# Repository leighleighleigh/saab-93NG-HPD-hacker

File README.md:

# saab-93NG-HPD-hacker
A reverse-engineering and interfacing board for the Saab Information Display / High Position Display, on 2003-2006 9-3 (Second Generation) Models.

## Project Status (DEC **2021**)
The **third** prototype of the PCB has been assembled and tested, as of August **2020**.
During this testing period, mild success was had, and some text/images were displayed. The full protocol is yet to be determined.

## Protocol Reverse Engineering
Please see [UART PROTOCOL](/UART_PROTOCOL.md) 

## Hardware Diagram
### Full In-car System

### HPD Interface v3 Internals (WIP)
The HPD hacker is unusual in that it utilises a dedicated UART interface accesible over SPI.
This eliminates the need for dedicated UART interfaces on the host microcontroller, which was a concern when the original design targeted the ESP8266.
The ESP32 series has enough hardware UARTs to do this on it's own, which will be utilised in the next hardware revision.

## Project structure
```bash
├── data_dumps # Raw UART data, CSV files exported from 'KingstVIS' software
├── hardware # KICAD v5+ projects
├── media # Images and diagrams
├── software # PlatformIO projects for the microcontrollers used here
└── PROTOCOL.md # This is where the results of our efforts is stored
```

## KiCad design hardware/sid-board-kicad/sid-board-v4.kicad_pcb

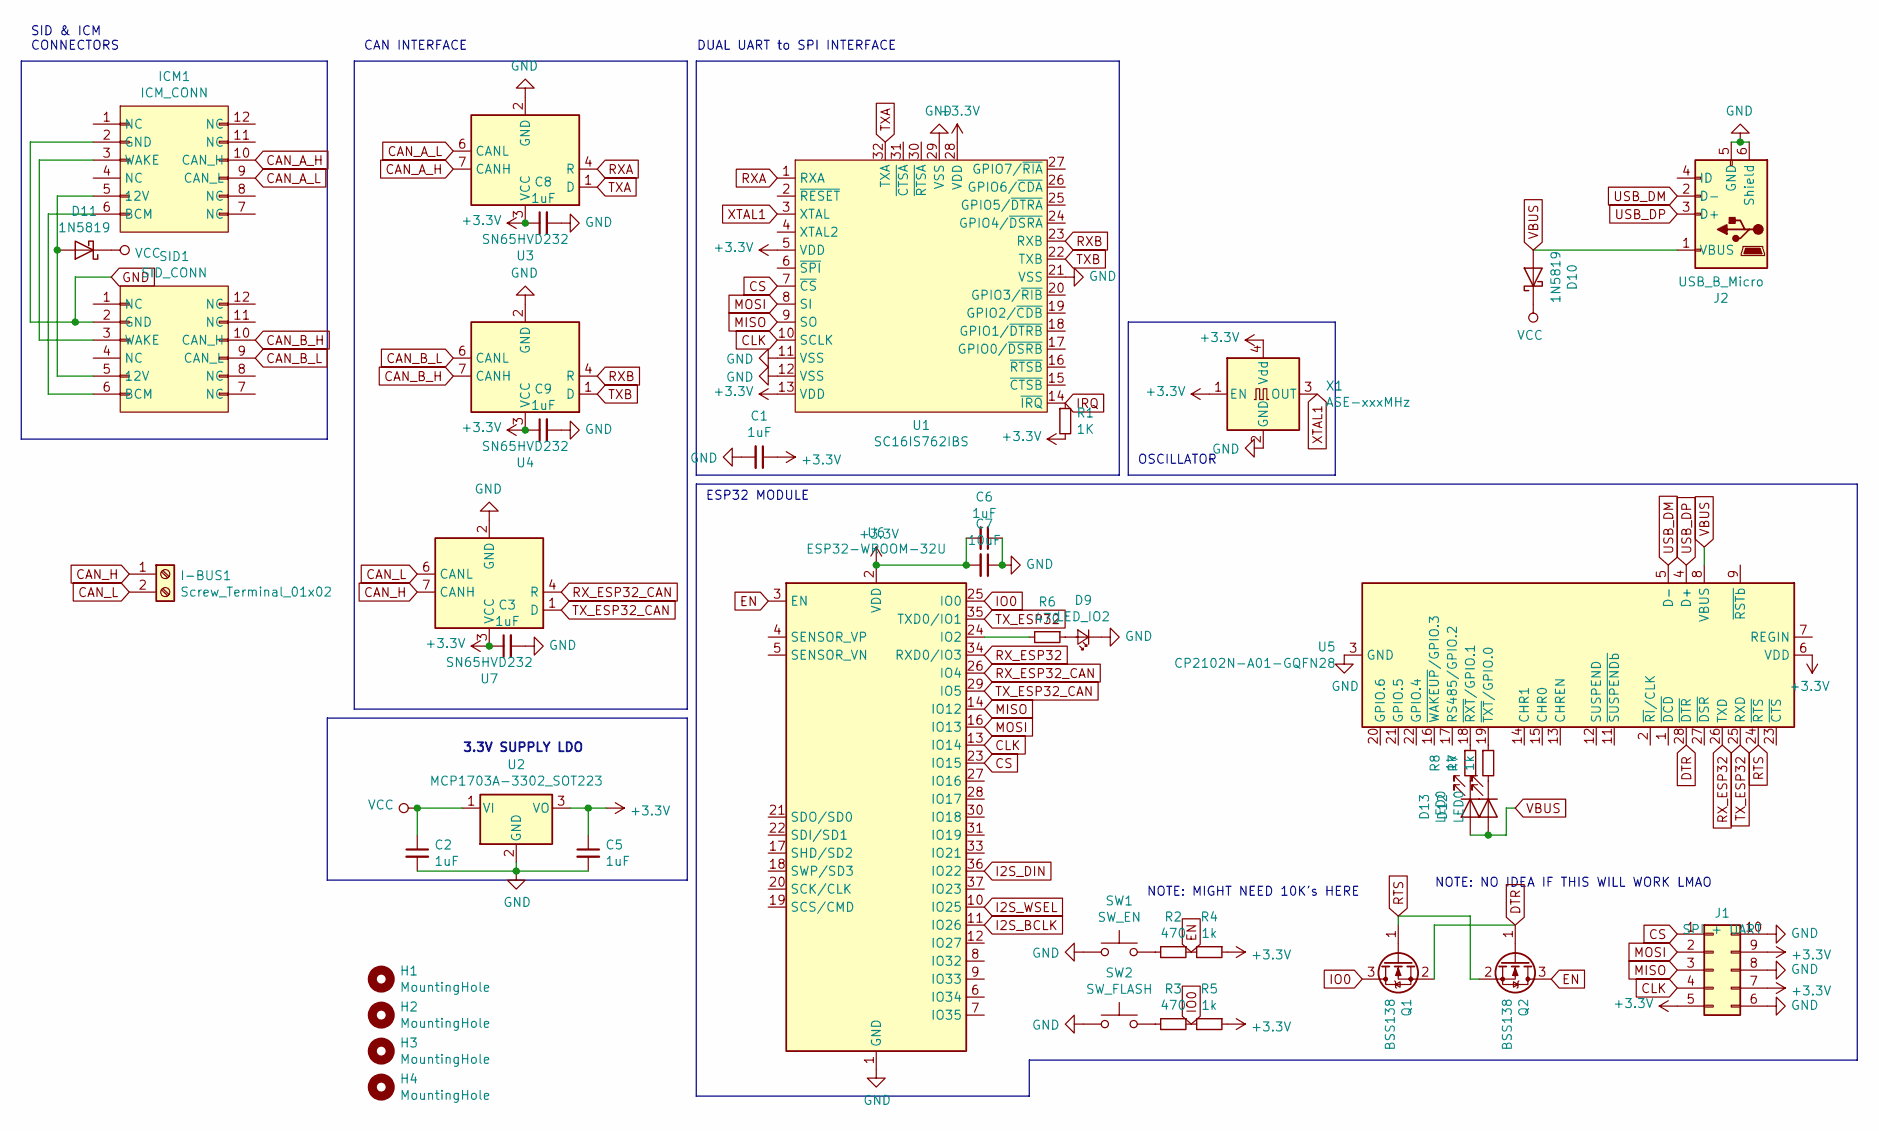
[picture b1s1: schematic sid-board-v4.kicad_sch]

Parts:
C1, C2, C3, C5, C6, C8, C9: 1uF; C_0805_2012Metric_Pad1.15x1.40mm_HandSolder
C7: 10uF; CP_EIA-6032-20_AVX-F_Pad2.25x2.35mm_HandSolder
D9: LED_IO2; LED_0805_2012Metric_Pad1.15x1.40mm_HandSolder
D10, D11: 1N5819; D_SOD-123
D12, D13: LED0; LED_0805_2012Metric_Pad1.15x1.40mm_HandSolder
H1, H2, H3, H4: MountingHole; MountingHole_4.3mm_M4_Pad_Via
I-BUS1: Screw_Terminal_01x02; TerminalBlock_Phoenix_MKDS-1,5-2-5.08_1x02_P5.08mm_Horizont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
ICM1: ICM_CONN; SAAB_SID_CONNECTOR_HEADER
J1: SPI + UART; PinHeader_2x05_P2.00mm_Vertical
J2: USB_B_Micro; USB_Micro-B_Molex-105017-0001
Q1, Q2: BSS138; SOT-23
R1: 1K; R_0805_2012Metric_Pad1.15x1.40mm_HandSolder
R2, R3, R6: 470; R_0805_2012Metric_Pad1.15x1.40mm_HandSolder
R4, R5, R7, R8: 1k; R_0805_2012Metric_Pad1.15x1.40mm_HandSolder
SID1: SID_CONN; SAAB_SID_CONNECTOR_HEADER
SW1: SW_EN; SW_Push_SPST_NO_Alps_SKRK
SW2: SW_FLASH; SW_Push_SPST_NO_Alps_SKRK
U1: SC16IS762IBS; VQFN-32-1EP_5x5mm_P0.5mm_EP3.1x3.1mm
U2: MCP1703A-3302_SOT223; SOT-223-3_TabPin2
U3, U4, U7: SN65HVD232; SOIC-8_3.9x4.9mm_P1.27mm
U5: CP2102N-A01-GQFN28; QFN-28-1EP_5x5mm_P0.5mm_EP3.35x3.35mm
U6: ESP32-WROOM-32U
X1: ASE-xxxMHz; Oscillator_SMD_EuroQuartz_XO53-4Pin_5.0x3.2mm_HandSoldering

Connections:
+3V3: C1.1, C3.1, C5.1, C6.2, C7.2, C8.1, C9.1, J1.5, J1.7, J1.9, R1.2, R4.1, R5.1, U1.5 (VDD), U1.13 (VDD), U1.28 (VDD), U2.3 (VO), U3.3 (VCC), U4.3 (VCC), U5.6 (VDD), U6.2 (VDD), U7.3 (VCC), X1.1 (EN), X1.4 (Vdd)
CAN_A_H: ICM1.10 (CAN_H), U3.7 (CANH)
CAN_A_L: ICM1.9 (CAN_L), U3.6 (CANL)
CAN_B_H: SID1.10 (CAN_H), U4.7 (CANH)
CAN_B_L: SID1.9 (CAN_L), U4.6 (CANL)
CAN_H: I-BUS1.1, U7.7 (CANH)
CAN_L: I-BUS1.2, U7.6 (CANL)
CLK: J1.4, U1.10 (SCLK), U6.13 (IO14)
CS: J1.1, U1.7 (~CS), U6.23 (IO15)
DTR: Q1.2 (S), Q2.1 (G), U5.28 (~DTR)
EN: Q2.3 (D), R2.1, R4.2, U6.3 (EN)
GND: C1.2, C2.2, C3.2, C5.2, C6.1, C7.1, C8.2, C9.2, D9.1 (K), ICM1.2 (GND), J1.6, J1.8, J1.10, J2.5 (GND), J2.6 (Shield), SID1.2 (GND), SW1.1, SW2.1, U1.11 (VSS), U1.12 (VSS), U1.21 (VSS), U1.29 (VSS), U2.2 (GND), U3.2 (GND), U4.2 (GND), U5.3 (GND), U5.29 (GND), U6.1 (GND), U6.15 (GND), U6.38 (GND), U6.39 (GND), U7.2 (GND), X1.2 (GND); also elsewhere on the board
I2S_BCLK: U6.11 (IO26)
I2S_DIN: U6.36 (IO22)
I2S_WSEL: U6.10 (IO25)
IO0: Q1.3 (D), R3.1, R5.2, U6.25 (IO0)
IRQ: R1.1, U1.14 (~IRQ)
MISO: J1.3, U1.9 (SO), U6.14 (IO12)
MOSI: J1.2, U1.8 (SI), U6.16 (IO13)
unnamed: D9.2 (A), R6.1
unnamed: D11.2 (A), ICM1.5 (12V), SID1.5 (12V)
unnamed: D12.1 (K), R7.2
unnamed: D13.1 (K), R8.2
unnamed: ICM1.3 (WAKE), SID1.3 (WAKE)
unnamed: ICM1.6 (BCM), SID1.6 (BCM)
unnamed: R2.2, SW1.2
unnamed: R3.2, SW2.2
unnamed: R6.2, U6.24 (IO2)
unnamed: R7.1, U5.19 (~TXT~/GPIO.0)
unnamed: R8.1, U5.18 (~RXT~/GPIO.1)
RTS: Q1.1 (G), Q2.2 (S), U5.24 (~RTS)
RXA: U1.1 (RXA), U3.4 (R)
RXB: U1.23 (RXB), U4.4 (R)
RX_ESP32: U5.26 (TXD), U6.34 (RXD0/IO3)
RX_ESP32_CAN: U6.26 (IO4), U7.4 (R)
TXA: U1.32 (TXA), U3.1 (D)
TXB: U1.22 (TXB), U4.1 (D)
TX_ESP32: U5.25 (RXD), U6.35 (TXD0/IO1)
TX_ESP32_CAN: U6.29 (IO5), U7.1 (D)
USB_DM: J2.2 (D-), U5.5 (D-); also elsewhere on the board
USB_DP: J2.3 (D+), U5.4 (D+); also elsewhere on the board
VBUS: D10.2 (A), D12.2 (A), D13.2 (A), J2.1 (VBUS), U5.8 (VBUS); also elsewhere on the board
VCC: C2.1, D10.1 (K), D11.1 (K), U2.1 (VI)
XTAL1: U1.3 (XTAL), X1.3 (OUT)

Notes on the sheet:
SID & ICM CONNECTORS
CAN INTERFACE
3.3V SUPPLY LDO
DUAL UART to SPI INTERFACE
ESP32 MODULE
OSCILLATOR
NOTE: MIGHT NEED 10K's HERE
NOTE: NO IDEA IF THIS WILL WORK LMAO

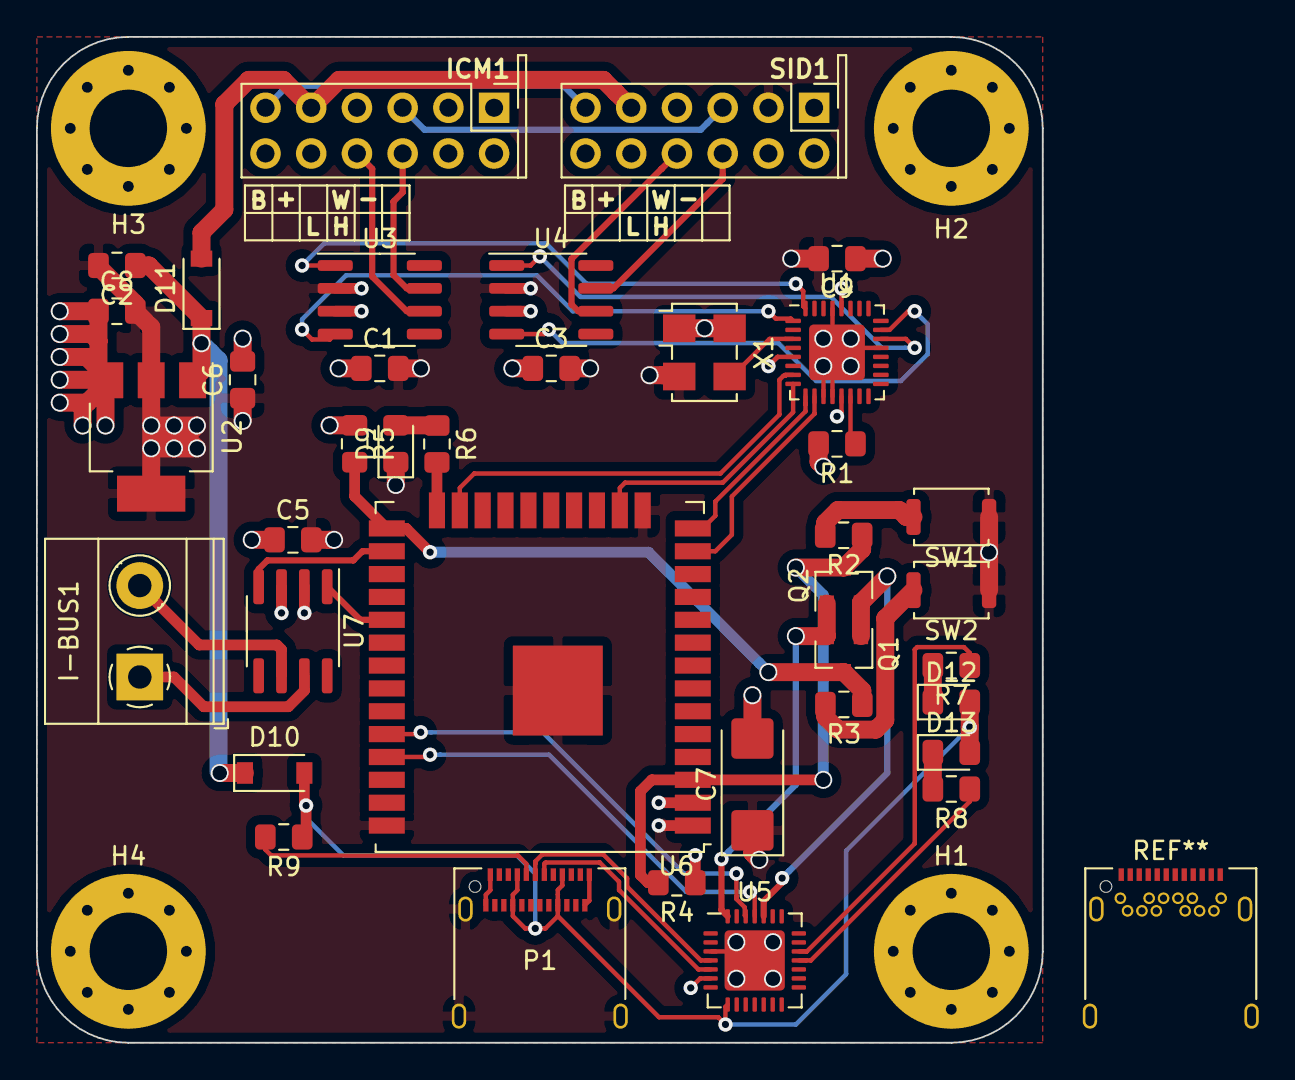
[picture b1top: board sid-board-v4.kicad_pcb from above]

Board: 4 copper layers, 55.9 x 55.9 mm, 42 parts (0 on the bottom side), 42 nets.

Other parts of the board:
P1: USB_C_Plug_USB2.0; USB_C_Receptacle_Amphenol_12401610E4-2A
R9: 56k; R_0805_2012Metric_Pad1.15x1.40mm_HandSolder

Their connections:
GND: P1.A1, P1.A12, P1.B1, P1.B12, P1.S1; also elsewhere on the board
unnamed: P1.A5, R9.2
USB_DM: P1.A7; also elsewhere on the board
USB_DP: P1.A6; also elsewhere on the board
VBUS: P1.A4, P1.A9, P1.B4, P1.B9, R9.1; also elsewhere on the board

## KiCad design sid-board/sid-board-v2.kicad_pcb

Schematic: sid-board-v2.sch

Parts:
C1, C4: 100nF; C_0805_2012Metric_Pad1.15x1.40mm_HandSolder
D1: LED7; LED_0805_2012Metric_Pad1.15x1.40mm_HandSolder
D2: LED6; LED_0805_2012Metric_Pad1.15x1.40mm_HandSolder
D3: LED5; LED_0805_2012Metric_Pad1.15x1.40mm_HandSolder
D4: LED4; LED_0805_2012Metric_Pad1.15x1.40mm_HandSolder
D5: LED3; LED_0805_2012Metric_Pad1.15x1.40mm_HandSolder
D6: LED2; LED_0805_2012Metric_Pad1.15x1.40mm_HandSolder
D7: LED1; LED_0805_2012Metric_Pad1.15x1.40mm_HandSolder
D8: LED0; LED_0805_2012Metric_Pad1.15x1.40mm_HandSolder
ICM1: ICM_CONN; SAAB_SID_CONNECTOR_HEADER
J1: SPI+IRQ+POWER; PinSocket_2x04_P2.54mm_Vertical
Q1, Q2, Q3, Q4: BSS138; SOT-23
R1, R11, R12, R13, R14, R15, R16, R17, R18: 1K; R_0805_2012Metric_Pad1.15x1.40mm_HandSolder
R3, R4, R5, R6, R7, R8, R9, R10: 10k; R_0805_2012Metric_Pad1.15x1.40mm_HandSolder
SID1: SID_CONN; SAAB_SID_CONNECTOR_HEADER
U1: SC16IS752IPW; TSSOP-28_4.4x9.7mm_P0.65mm
U2: MCP1703A-3302_SOT223; SOT-223-3_TabPin2
U3, U4: PCA82C250; SOIC-8_3.9x4.9mm_P1.27mm
U5: MCP1703A-5002_SOT223; SOT-223-3_TabPin2
X1: S53305-16.000-X

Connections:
CLK: J1.1, U1.13 (SCLK)
CS: J1.4, U1.10 (~CS)
GND: C1.2, C4.2, D1.1 (K), D2.1 (K), D3.1 (K), D4.1 (K), D5.1 (K), D6.1 (K), D7.1 (K), D8.1 (K), ICM1.2 (GND), J1.5, SID1.2 (GND), U1.9 (I2C/~SPI), U1.14 (VSS), U1.22 (VSS), U2.2 (GND), U3.2 (GND), U3.8 (Rsl), U4.2 (GND), U4.8 (Rsl), U5.2 (GND), X1.2
IRQ: J1.8, R1.1, U1.15 (~IRQ)
MISO: J1.2, U1.12 (MISO)
MOSI: J1.3, U1.11 (MOSI)
unnamed: D1.2 (A), R11.2
unnamed: D2.2 (A), R12.2
unnamed: D3.2 (A), R13.2
unnamed: D4.2 (A), R14.2
unnamed: D5.2 (A), R15.2
unnamed: D6.2 (A), R16.2
unnamed: D7.2 (A), R17.2
unnamed: D8.2 (A), R18.2
unnamed: ICM1.3 (WAKE), SID1.3 (WAKE)
unnamed: ICM1.6 (BCM), SID1.6 (BCM)
unnamed: ICM1.9 (CAN_H), U3.7 (CAN+)
unnamed: ICM1.10 (CAN_L), U3.6 (CAN-)
unnamed: R11.1, U1.28 (GPIO7/~RIA)
unnamed: R12.1, U1.27 (GPIO6/~CDA)
unnamed: R13.1, U1.26 (GPIO5/~DTRA)
unnamed: R14.1, U1.25 (GPIO4/~DSRA)
unnamed: R15.1, U1.21 (GPIO3/~RIB)
unnamed: R16.1, U1.20 (GPIO2/~CDB)
unnamed: R17.1, U1.19 (GPIO1/~DTRB)
unnamed: R18.1, U1.18 (GPIO0/~DSRB)
unnamed: SID1.9 (CAN_H), U4.7 (CAN+)
unnamed: SID1.10 (CAN_L), U4.6 (CAN-)
RXA: Q2.2 (S), R4.2, U1.4 (RXA)
RXA_CMOS: Q2.3 (D), R3.2, U3.4 (RxD)
RXB: Q4.2 (S), R8.2, U1.24 (RXB)
RXB_CMOS: Q4.3 (D), R7.2, U4.4 (RxD)
TXA: Q3.2 (S), R6.2, U1.3 (TXA)
TXA_CMOS: Q3.3 (D), R5.2, U3.1 (TxD)
TXB: Q1.2 (S), R10.2, U1.23 (TXB)
TXB_CMOS: Q1.3 (D), R9.2, U4.1 (TxD)
VDD_3.3V: C4.1, J1.6, Q1.1 (G), Q2.1 (G), Q3.1 (G), Q4.1 (G), R1.2, R4.1, R6.1, R8.1, R10.1, U1.5 (~RESET), U1.8 (VDD), U2.3 (VO), X1.1, X1.4
VDD_5V: C1.1, J1.7, R3.1, R5.1, R7.1, R9.1, U3.3 (VCC), U4.3 (VCC), U5.3 (VO)
VIN: ICM1.5 (12V), SID1.5 (12V), U2.1 (VI), U5.1 (VI)
XTAL1: U1.6 (XTAL1), X1.3

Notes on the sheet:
3.3V SUPPLY LDO
5V SUPPLY LDO
SID & ICM CONNECTORS
CAN INTERFACE
DUAL UART to SPI INTERFACE
OSCILLATOR
CMOS to TTL 5V TO 3.3V BIDIRECTIONAL LEVEL SHIFTER
GPIO LED OUTPUT

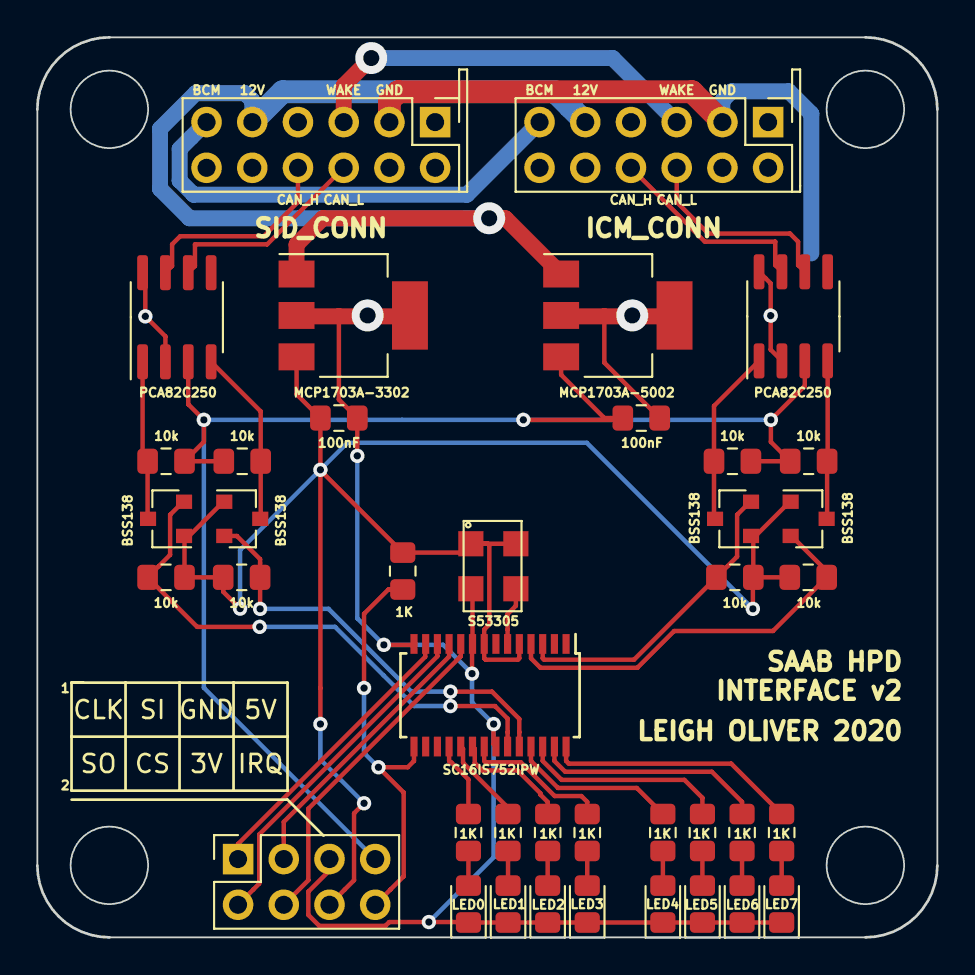
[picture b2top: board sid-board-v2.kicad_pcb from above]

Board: 2 copper layers, 50.0 x 50.0 mm, 40 parts (0 on the bottom side), 40 nets.

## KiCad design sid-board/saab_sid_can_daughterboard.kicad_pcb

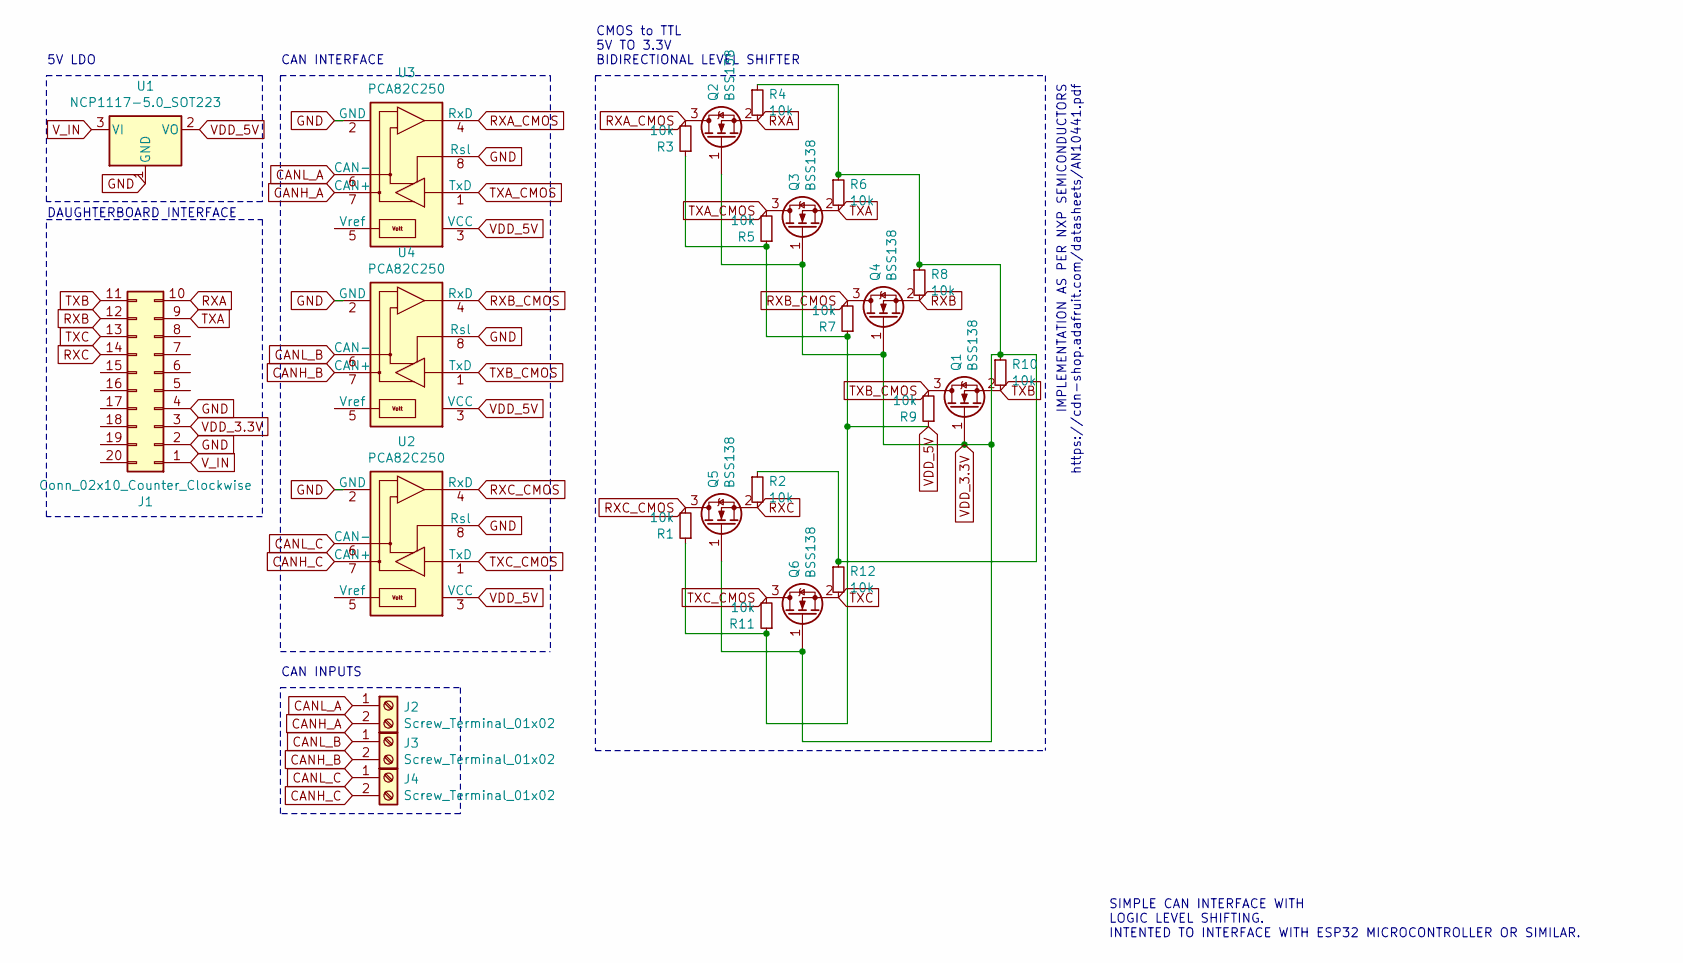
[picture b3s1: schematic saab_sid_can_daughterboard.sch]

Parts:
J1: Conn_02x10_Counter_Clockwise; PinSocket_2x10_P2.54mm_Vertical
J2, J3, J4: Screw_Terminal_01x02; TerminalBlock_Phoenix_MKDS-1,5-2-5.08_1x02_P5.08mm_Horizont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
Q1, Q2, Q3, Q4, Q5, Q6: BSS138; SOT-23
R1, R2, R3, R4, R5, R6, R7, R8, R9, R10, R11, R12: 10k; R_0805_2012Metric_Pad1.15x1.40mm_HandSolder
U1: NCP1117-5.0_SOT223; SOT-223-3_TabPin2
U2, U3, U4: PCA82C250; SOIC-8_3.9x4.9mm_P1.27mm

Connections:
CANH_A: J2.2, U3.7 (CAN+)
CANH_B: J3.2, U4.7 (CAN+)
CANH_C: J4.2, U2.7 (CAN+)
CANL_A: J2.1, U3.6 (CAN-)
CANL_B: J3.1, U4.6 (CAN-)
CANL_C: J4.1, U2.6 (CAN-)
GND: J1.2, J1.4, U1.1 (GND), U2.2 (GND), U2.8 (Rsl), U3.2 (GND), U3.8 (Rsl), U4.2 (GND), U4.8 (Rsl)
RXA: J1.10, Q2.2 (S), R4.2
RXA_CMOS: Q2.3 (D), R3.2, U3.4 (RxD)
RXB: J1.12, Q4.2 (S), R8.2
RXB_CMOS: Q4.3 (D), R7.2, U4.4 (RxD)
RXC: J1.14, Q5.2 (S), R2.2
RXC_CMOS: Q5.3 (D), R1.2, U2.4 (RxD)
TXA: J1.9, Q3.2 (S), R6.2
TXA_CMOS: Q3.3 (D), R5.2, U3.1 (TxD)
TXB: J1.11, Q1.2 (S), R10.2
TXB_CMOS: Q1.3 (D), R9.2, U4.1 (TxD)
TXC: J1.13, Q6.2 (S), R12.2
TXC_CMOS: Q6.3 (D), R11.2, U2.1 (TxD)
VDD_3.3V: J1.3, Q1.1 (G), Q2.1 (G), Q3.1 (G), Q4.1 (G), Q5.1 (G), Q6.1 (G), R2.1, R4.1, R6.1, R8.1, R10.1, R12.1
VDD_5V: R1.1, R3.1, R5.1, R7.1, R9.1, R11.1, U1.2 (VO), U2.3 (VCC), U3.3 (VCC), U4.3 (VCC)
V_IN: J1.1, U1.3 (VI)

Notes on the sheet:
CAN INTERFACE
CMOS to TTL 5V TO 3.3V BIDIRECTIONAL LEVEL SHIFTER
IMPLEMENTATION AS PER NXP SEMICONDUCTORS https://cdn-shop.adafruit.com/datasheets/AN10441.pdf
SIMPLE CAN INTERFACE WITH LOGIC LEVEL SHIFTING. INTENTED TO INTERFACE WITH ESP32 MICROCONTROLLER OR SIMILAR.
5V LDO
CAN INPUTS
DAUGHTERBOARD INTERFACE

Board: 2 copper layers, 26 parts (1 on the bottom side), 22 nets, no tracks yet.

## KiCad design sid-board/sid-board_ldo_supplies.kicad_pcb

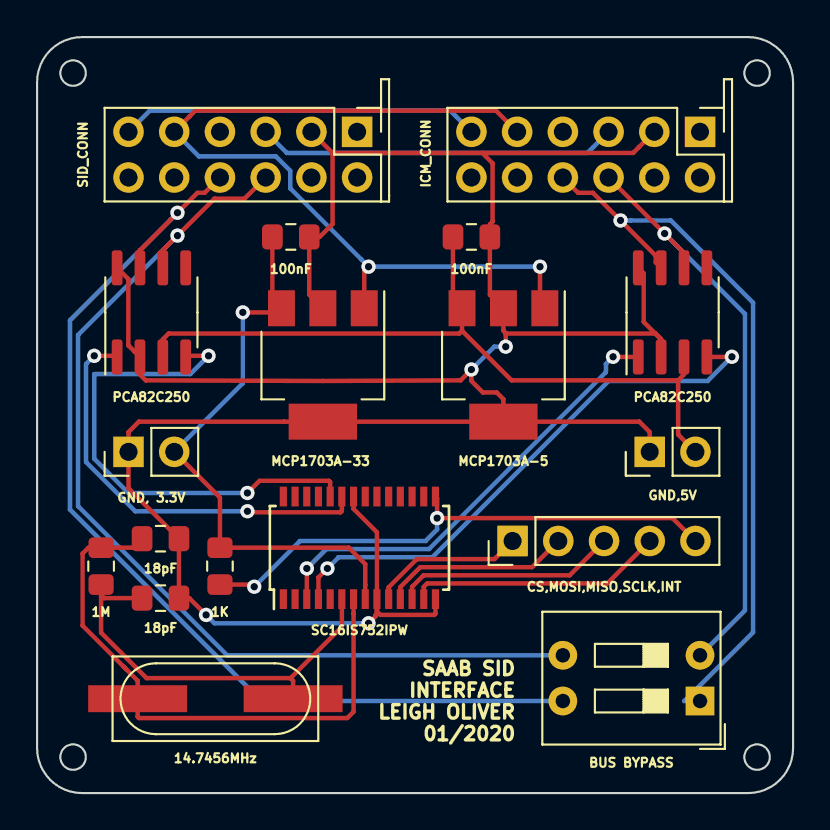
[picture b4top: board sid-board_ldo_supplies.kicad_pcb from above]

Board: 2 copper layers, 42.0 x 42.0 mm, 18 parts (0 on the bottom side), 21 nets.

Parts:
BUS BYPASS: SW_DIP_x02; SW_DIP_SPSTx02_Slide_9.78x7.26mm_W7.62mm_P2.54mm
C1, C4: 100nF; C_0805_2012Metric_Pad1.15x1.40mm_HandSolder
C2, C3: 18pF; C_0805_2012Metric_Pad1.15x1.40mm_HandSolder
J1: ICM_CONN; SAAB_SID_CONNECTOR_HEADER
J2: SID_CONN; SAAB_SID_CONNECTOR_HEADER
J3: GND,5V; PinHeader_1x02_P2.54mm_Vertical
J4: GND, 3.3V; PinHeader_1x02_P2.54mm_Vertical
J5: CS,MOSI,MISO,SCLK,INT; PinHeader_1x05_P2.54mm_Vertical
R1: 1K; R_0805_2012Metric_Pad1.15x1.40mm_HandSolder
R2: 1M; R_0805_2012Metric_Pad1.15x1.40mm_HandSolder
U1: SC16IS752IPW; TSSOP-28_4.4x9.7mm_P0.65mm
U2: MCP1703A-33; SOT-223-3_TabPin2
U3, U4: PCA82C250; SOIC-8_3.9x4.9mm_P1.27mm
U5: MCP1703A-5; SOT-223-3_TabPin2
Y1: 14.7456MHz; Euroquarts 14.7456MHz Crystal ±30ppm SMD 2-Pin 12.4 x 4.5 x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

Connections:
GND: C1.2, C2.2, C3.2, C4.2, J1.2, J2.2, J3.1, J4.1, U1.9, U1.14, U1.22, U2.2, U3.2, U3.8, U4.2, U4.8, U5.2
unnamed: J1.3, J2.3
unnamed: J1.6, J2.6
unnamed: BUS BYPASS.1, J1.9, U3.7
unnamed: BUS BYPASS.2, J1.10, U3.6
unnamed: BUS BYPASS.4, J2.9, U4.7
unnamed: BUS BYPASS.3, J2.10, U4.6
unnamed: J5.1, U1.10
unnamed: J5.2, U1.11
unnamed: J5.3, U1.12
unnamed: J5.4, U1.13
unnamed: J5.5, R1.1, U1.15
unnamed: U1.3, U3.1
unnamed: U1.4, U3.4
unnamed: U1.23, U4.1
unnamed: U1.24, U4.4
VDD_3.3V: C4.1, J4.2, R1.2, U1.8, U2.3
VDD_5V: C1.1, J3.2, U3.3, U4.3, U5.3
VIN: J1.5, J2.5, U2.1, U5.1
XTAL1: C3.1, R2.1, U1.6, Y1.2
XTAL2: C2.1, R2.2, U1.7, Y1.1

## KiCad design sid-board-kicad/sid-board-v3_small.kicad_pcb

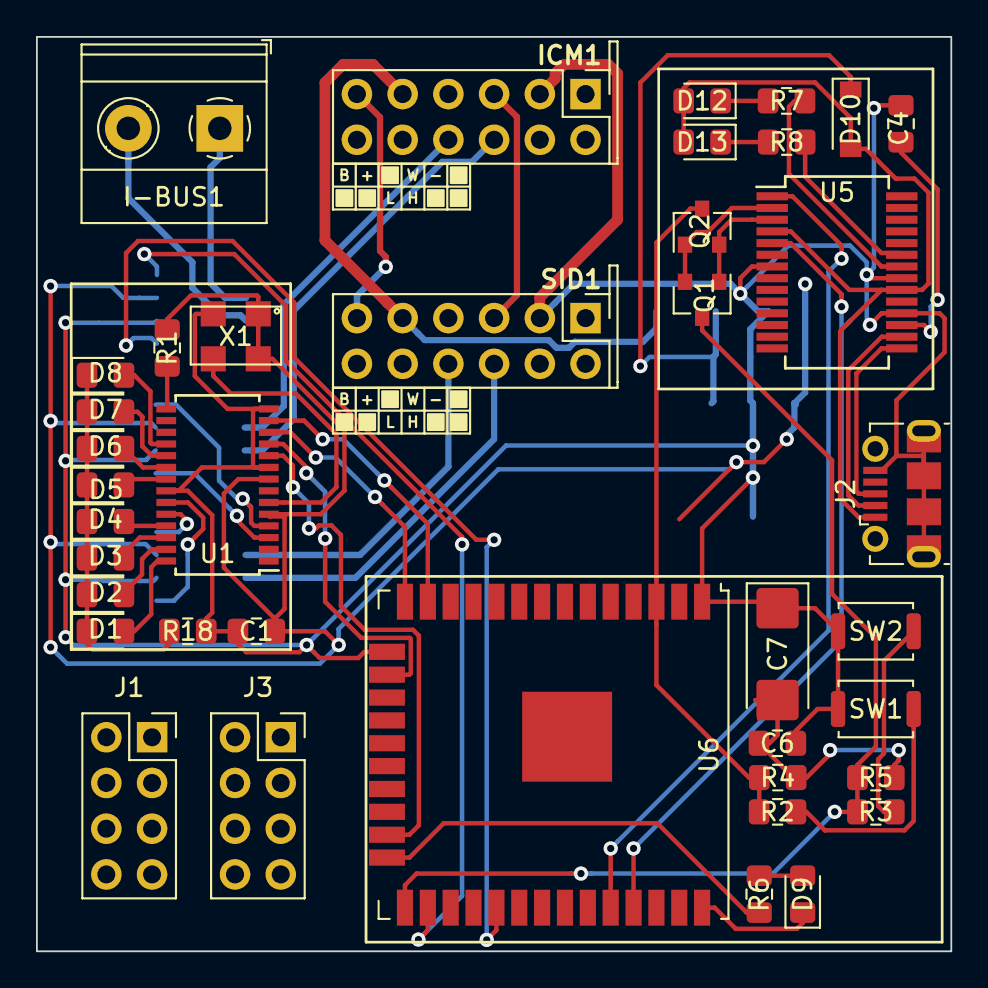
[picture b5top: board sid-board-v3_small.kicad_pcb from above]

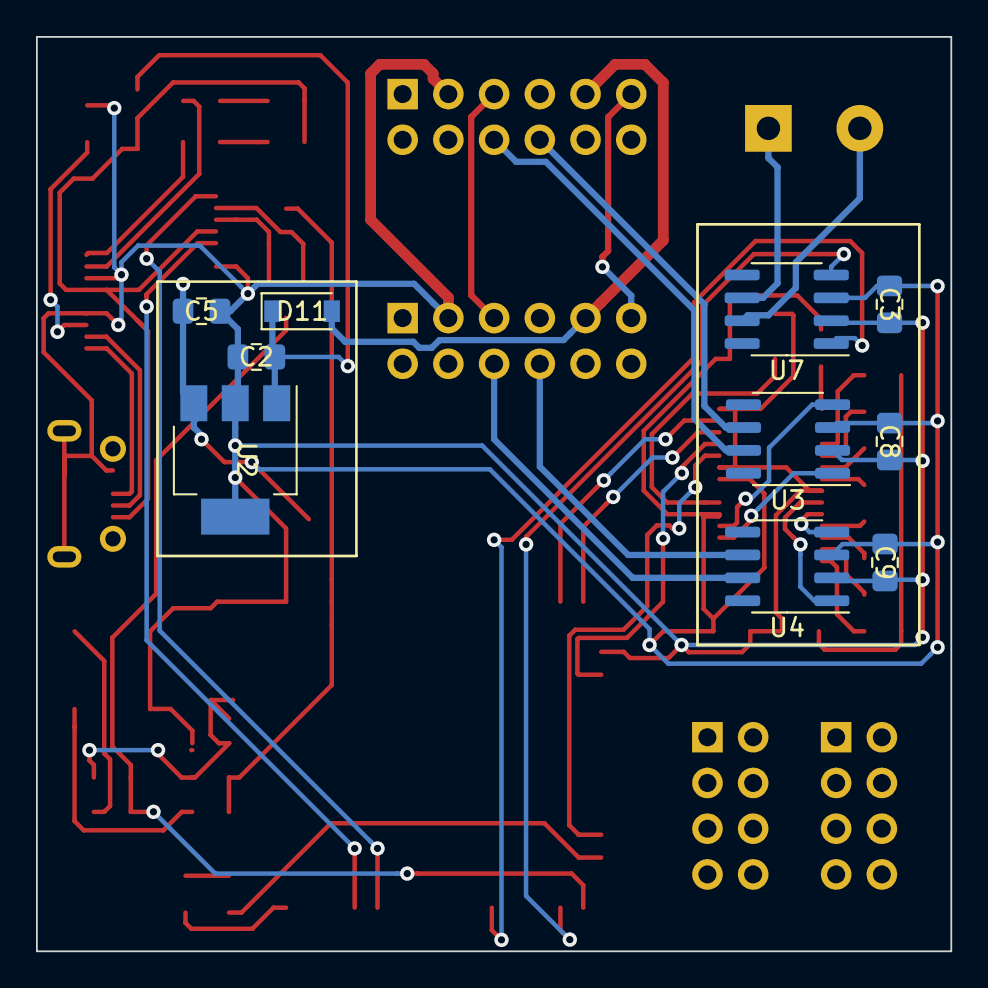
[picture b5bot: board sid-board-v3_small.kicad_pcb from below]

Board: 2 copper layers, 50.8 x 50.8 mm, 49 parts (10 on the bottom side), 51 nets.

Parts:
C1, C2, C3, C4, C5, C6, C8, C9: 1uF; C_0805_2012Metric_Pad1.15x1.40mm_HandSolder
C7: 10uF; CP_EIA-6032-20_AVX-F_Pad2.25x2.35mm_HandSolder
D1: LED7; LED_0805_2012Metric_Pad1.15x1.40mm_HandSolder
D2: LED6; LED_0805_2012Metric_Pad1.15x1.40mm_HandSolder
D3: LED5; LED_0805_2012Metric_Pad1.15x1.40mm_HandSolder
D4: LED4; LED_0805_2012Metric_Pad1.15x1.40mm_HandSolder
D5: LED3; LED_0805_2012Metric_Pad1.15x1.40mm_HandSolder
D6: LED2; LED_0805_2012Metric_Pad1.15x1.40mm_HandSolder
D7: LED1; LED_0805_2012Metric_Pad1.15x1.40mm_HandSolder
D8, D12, D13: LED0; LED_0805_2012Metric_Pad1.15x1.40mm_HandSolder
D9: LED_IO2; LED_0805_2012Metric_Pad1.15x1.40mm_HandSolder
D10, D11: 1N5819; D_SOD-123
I-BUS1: Screw_Terminal_01x02; TerminalBlock_Phoenix_MKDS-1,5-2-5.08_1x02_P5.08mm_Horizont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
ICM1: ICM_CONN; SAAB_SID_CONNECTOR_HEADER
J1: SPI + UART; PinSocket_2x04_P2.54mm_Vertical
J2: USB_B_Micro; USB_Micro-B_Molex-105017-0001
J3: UART; PinSocket_2x04_P2.54mm_Vertical
Q1, Q2: BSS138; SOT-23
R1, R18: 1K; R_0805_2012Metric_Pad1.15x1.40mm_HandSolder
R2, R3, R6: 470; R_0805_2012Metric_Pad1.15x1.40mm_HandSolder
R4, R5, R7, R8: 1k; R_0805_2012Metric_Pad1.15x1.40mm_HandSolder
SID1: SID_CONN; SAAB_SID_CONNECTOR_HEADER
SW1: SW_EN; SW_Push_SPST_NO_Alps_SKRK
SW2: SW_FLASH; SW_Push_SPST_NO_Alps_SKRK
U1: SC16IS752IPW; TSSOP-28_4.4x9.7mm_P0.65mm
U2: MCP1703A-3302_SOT223; SOT-223-3_TabPin2
U3, U4, U7: SN65HVD232; SOIC-8_3.9x4.9mm_P1.27mm
U5: CY7C65213-28PVXI; SSOP-28_5.3x10.2mm_P0.65mm
U6: ESP32-WROOM-32U
X1: S53305-24.000-X; S53305-16.000-X

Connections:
CAN_A_H: ICM1.10, U3.7
CAN_A_L: ICM1.9, U3.6
CAN_B_H: SID1.10, U4.7
CAN_B_L: SID1.9, U4.6
CAN_H: I-BUS1.2, U7.7
CAN_L: I-BUS1.1, U7.6
CLK: J1.2, U1.13, U6.13
CS: J1.1, U1.10, U6.23
DTR: Q1.2, Q2.1, U5.2
EN: Q2.3, R2.1, R4.2, U6.3
GND: C1.2, C2.2, C3.2, C4.2, C5.2, C6.1, C7.1, C8.2, C9.2, D9.1, ICM1.2, J1.5, J2.5, J2.6, J3.5, R18.2, SID1.2, SW1.1, SW2.1, U1.9, U1.14, U1.22, U2.2, U3.2, U4.2, U5.7, U5.18, U5.21, U6.1, U6.15, U6.38, U6.39, U7.2, X1.2
IO0: Q1.3, R3.1, R5.2, U6.25
IRQ: R1.1, U1.15
MISO: J1.4, U1.12, U6.14
MOSI: J1.3, U1.11, U6.16
unnamed: C4.1, U5.17
unnamed: D1.1, D2.1, D3.1, D4.1, D5.1, D6.1, D7.1, D8.1, R18.1
unnamed: D1.2, U1.28
unnamed: D2.2, U1.27
unnamed: D3.2, U1.26
unnamed: D4.2, U1.25
unnamed: D5.2, U1.21
unnamed: D6.2, U1.20
unnamed: D7.2, U1.19
unnamed: D8.2, U1.18
unnamed: D9.2, R6.1
unnamed: D11.2, ICM1.5, SID1.5
unnamed: D12.1, R7.2
unnamed: D13.1, R8.2
unnamed: ICM1.3, SID1.3
unnamed: ICM1.6, SID1.6
unnamed: R2.2, SW1.2
unnamed: R3.2, SW2.2
unnamed: R6.2, U6.24
unnamed: R7.1, U5.22
unnamed: R8.1, U5.23
RTS: Q1.1, Q2.2, U5.3
RXA: J1.8, U1.4, U3.4
RXB: J3.8, U1.24, U4.4
RX_ESP32: J3.2, U5.1, U6.34
RX_ESP32_CAN: J3.4, U6.26, U7.4
TXA: J1.7, U1.3, U3.1
TXB: J3.7, U1.23, U4.1
TX_ESP32: J3.1, U5.5, U6.35
TX_ESP32_CAN: J3.3, U6.29, U7.1
USB_DM: J2.2, U5.16
USB_DP: J2.3, U5.15
VBUS: D10.2, D12.2, D13.2, J2.1, U5.4, U5.20
VDD_3.3V: C1.1, C3.1, C5.1, C6.2, C7.2, C8.1, C9.1, J1.6, J3.6, R1.2, R4.1, R5.1, U1.5, U1.8, U2.3, U3.3, U4.3, U6.2, U7.3, X1.1, X1.4
VIN: C2.1, D10.1, D11.1, U2.1
XTAL1: U1.6, X1.3

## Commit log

2020-01-15 Added initial board layout, still working on it. Need to make silkscreen.
2020-01-15 Happy with first prototype, going to try get it made!
2020-01-21 Removed unnessecary cap, re-arranged.
2020-01-22 Working on new mostly-SMD version, switched to independant LDOs, added oscillator circuit.
2020-01-22 Re-did PCB layout, signifcantly smaller now.
2020-01-22 Layout and edgecut tweaks.
2020-01-22 Added 3d files for proper female sockets, havn't placed yet. Added text.
2020-01-22 Autorouted with Freerouting
2020-01-22 Updated manually routed board, removed debugging UART header.
2020-01-22 Autorouted vs Manual routed. Thinking about adding DIP switch.
2020-01-22 Edited some labels
2020-01-22 Added bypass DIP switch
2020-01-22 Added TODO text about putting interrupt connection back.
2020-01-26 FINAL BEFORE FABRICATION!
2020-01-26 Removed old plot files
2020-01-26 Removed old files
2020-01-26 Updated edge cuts
2020-02-10 Updated readme with prototype 1 notes.
2020-02-11 Added platformIO project, to interface a NodeMCU Esp8266 board over SPI.
2020-02-12 Updated README.md with more concise details.
2020-02-12 SID Board v2 in the making.
2020-02-12 Working on SIDBOARD2 layout
2020-02-12 Updated SPI layout and README.md
2020-02-12 Added an untested Loopback enable function, which sets bit4 of the MCR register.
2020-02-13 Finished draft layout of sid-board v2
2020-02-14 Working on routing of sidboard v2.
2020-02-15 Finished first draft PCB layout of SIDBOARD2
2020-02-15 Added experimental direct softwareserial interfacing
2020-02-15 Read-only test of SID-bus lines functional. Still trying to hone in on best baudrate to use.
2020-02-17 Added passthrough testing for dual CAN interface setup.
2020-02-17 Revised code after in-car testing
2020-02-17 Revised pinouts for perfboard proto
2020-02-17 Working on passthrough still. Probably a power issue.
2020-02-18 Passthrough getting closer. CAN interfaces seem to work, but the SID isn't doing anything. It's not boot looping anymore though.
2020-02-18 Added SID can bus observations
2020-02-26 Added simple loopback testing in the testMode=true portion of direct sw serial main.cpp. WORKS!
2020-02-26 Added beginnings of ICM,SID daughterboard module.
2020-02-26 Added beginnings of CAN daughterboard
2020-02-27 Loopback test mode complete. Working on buffer-then-send main function.
2020-02-27 Initial buffer-then-send trial
2020-02-27 Things are getting desperate. Tried a direct IO method, not working. Need to whip out oscilloscope.
2020-02-27 Working on CAN daughterboard
2020-03-06 Removed old boards projects
2020-03-07 Simplified serial passthrough
2020-03-08 Having buffer re-write issues. This makes a feedback loop. Need to brainstorm and debug this...
2020-03-09 Added ESP32 hardware sketch to try out, hopefully it overcomes SoftSerial limitations.
2020-03-14 Removed old projects, making great progress with I2C bridging.
2020-03-15 basic I2C bridge constructed, untested
2020-03-15 Fixed Serial always listening issue
2020-03-15 Added slave to master i2c test routine, identifies bad breadboard in prototype
2020-03-15 Working on software serial approach again
2020-03-15 Updated gitignore
2020-03-15 Working on state-based software serial sketch
2020-03-15 Still struggling with swserial
2020-03-21 Added new SCI16 project
2020-03-24 Added new custom footprint for crystal oscillator module, replacing the old crystal module
2020-03-24 Replaced crystal with oscillator module on PCB
2020-03-27 Working on arduino sketch
2020-04-07 Working on turn based Serial Comms
2020-04-07 Sitll no working UART passthrough
2020-05-08 Removed old daughterboard concept
2020-05-15 Cleaned up v2 board for prototype production
2020-05-16 Project re-organisation.
2020-05-16 Moved PROTOCOL.md file to software folder.
2020-05-25 Updating software for recv
2020-05-29 20% compensation for baudrate
2020-05-31 Updated README.md with prototype 2 results. Updated some code with testing stuff.
2020-08-02 Progress on hardware serial interface via websockets
2020-08-02 Working on protocol
2020-08-02 Added analysis script
2020-08-04 Implemented general websockets to uart interface
2020-08-04 Setup on mobile hotspot
2020-08-04 Collected log of bootup sequence
2020-08-04 Trying to read from screen file
2020-08-05 Got text to display from a captured loggit add -A!
2020-08-05 FINALLY
2020-08-05 Extended python script for rapid reverse-engineering
2020-08-05 Making progress on understanding the commands
2020-08-05 Example send_cmds_from_file will show multiple icons and fonts
2020-08-05 Messing with icons
2020-08-08 Writing utility functions in python to further explore text rendering possibilities
2020-08-08 Example layout in drawing_re.py
2020-08-08 Experimenting with unknown commands
2020-08-08 Custom ram icons showing up
2020-08-08 Tryign to get ram icons working
2020-08-08 Converted to a more robust serial approach
2020-08-10 Working on V3 board
2020-08-10 Assigned basic footprints
2020-08-10 Added UART interface to the SID BOARD V3
2020-08-10 Initial grouped PCB layout
2020-08-10 Experimenting with PCB layouts
2020-08-11 Crazy routing
2020-08-11 Improved routing in new version
2020-08-12 Redid routing more logically
2020-08-12 Happy with routing, replaced oscillator, need to label.
2020-08-14 Moved labels
2020-08-14 Added compressed file
2020-08-14 Added IO expansion for free pins on ESP32
2020-08-16 Labelling and reorganisation
2020-08-16 Lost labelling. Moved debug header.
2020-08-17 Re-labelling everything
2020-08-17 More labelling
2020-08-18 Checked bootstrapping pins. Checked RX TX pins.
2020-08-18 Labelling.
2020-08-18 Prints for silkscreen design
2020-08-18 Plot output
2020-08-18 Organisation and added more details
2020-08-24 Playing with 4 layer ideas
2020-08-24 Layer 4 stuff
2020-08-25 Layer 4 experiments
2020-08-27 Added 10ks
2020-08-28 First succesfull blink sketch
2020-08-28 ESP32 SPI confirmed working
2020-08-28 Working HPD operation. Going to test passthrough mode tomorrow.
2020-08-28 Passthrough mode testing
2020-08-28 Collected working SAAB logs
2020-08-29 Drawing RE working, analysing log files
2020-08-29 Attempting to replace messages on the fly
2020-08-29 More log analysis
2020-09-04 I forgot what I was doing
2020-09-04 Refinement of serial interface, improved and tweaked baud rates, working on python scripts
2020-09-04 Confirmed multiple layers and such work
2020-09-04 Cleaning
2020-09-04 Extracted data captures to new format
2020-09-04 Playing with cmd logs
2020-09-05 Fixed buffer size issue
2020-09-05 Reverse engineering text formats
2020-09-06 Polled all commands and recorded results
2020-09-06 Something weird happening on 0x40
2020-09-06 Entry for 0x40
2020-09-06 Added dummy byte stuff
2020-09-06 Cant make 0x40 work
2020-09-08 Trying to get 33kbps on the ESP32 SJA1000
2020-09-08 Stuff
2020-09-08 Baud calculator working!
2020-09-08 Added CAN_SPEED_33KBPS mode to Arduino-CAN-Master
2020-09-09 Fake response mode added
2020-09-11 Added USBC port which I know exists
2020-09-15 Formatting
2021-12-26 README updated to reflect progress since late 2020
2021-12-26 Removed VSCODE settings.json
2021-12-26 Attempt to embed image
2021-12-26 Aligned image to center
2021-12-26 Image update
2021-12-26 data_dumps description update
2021-12-26 Fix typo in protocol document
2021-12-26 Document incomplete notice
2021-12-26 Fix image height
2021-12-26 Renaming of entire project
2021-12-26 Hardware Diagram added
2021-12-26 Embedded image using HTML
2021-12-26 Typo in image urls
2021-12-26 Fix markdown spacing
2021-12-26 Beginnings of a HPD Hacker diagram
2021-12-26 More diagram images
2021-12-26 Text align
2021-12-26 Change to headers
2021-12-26 WIP tag, note on v3
2021-12-26 Removed v4
